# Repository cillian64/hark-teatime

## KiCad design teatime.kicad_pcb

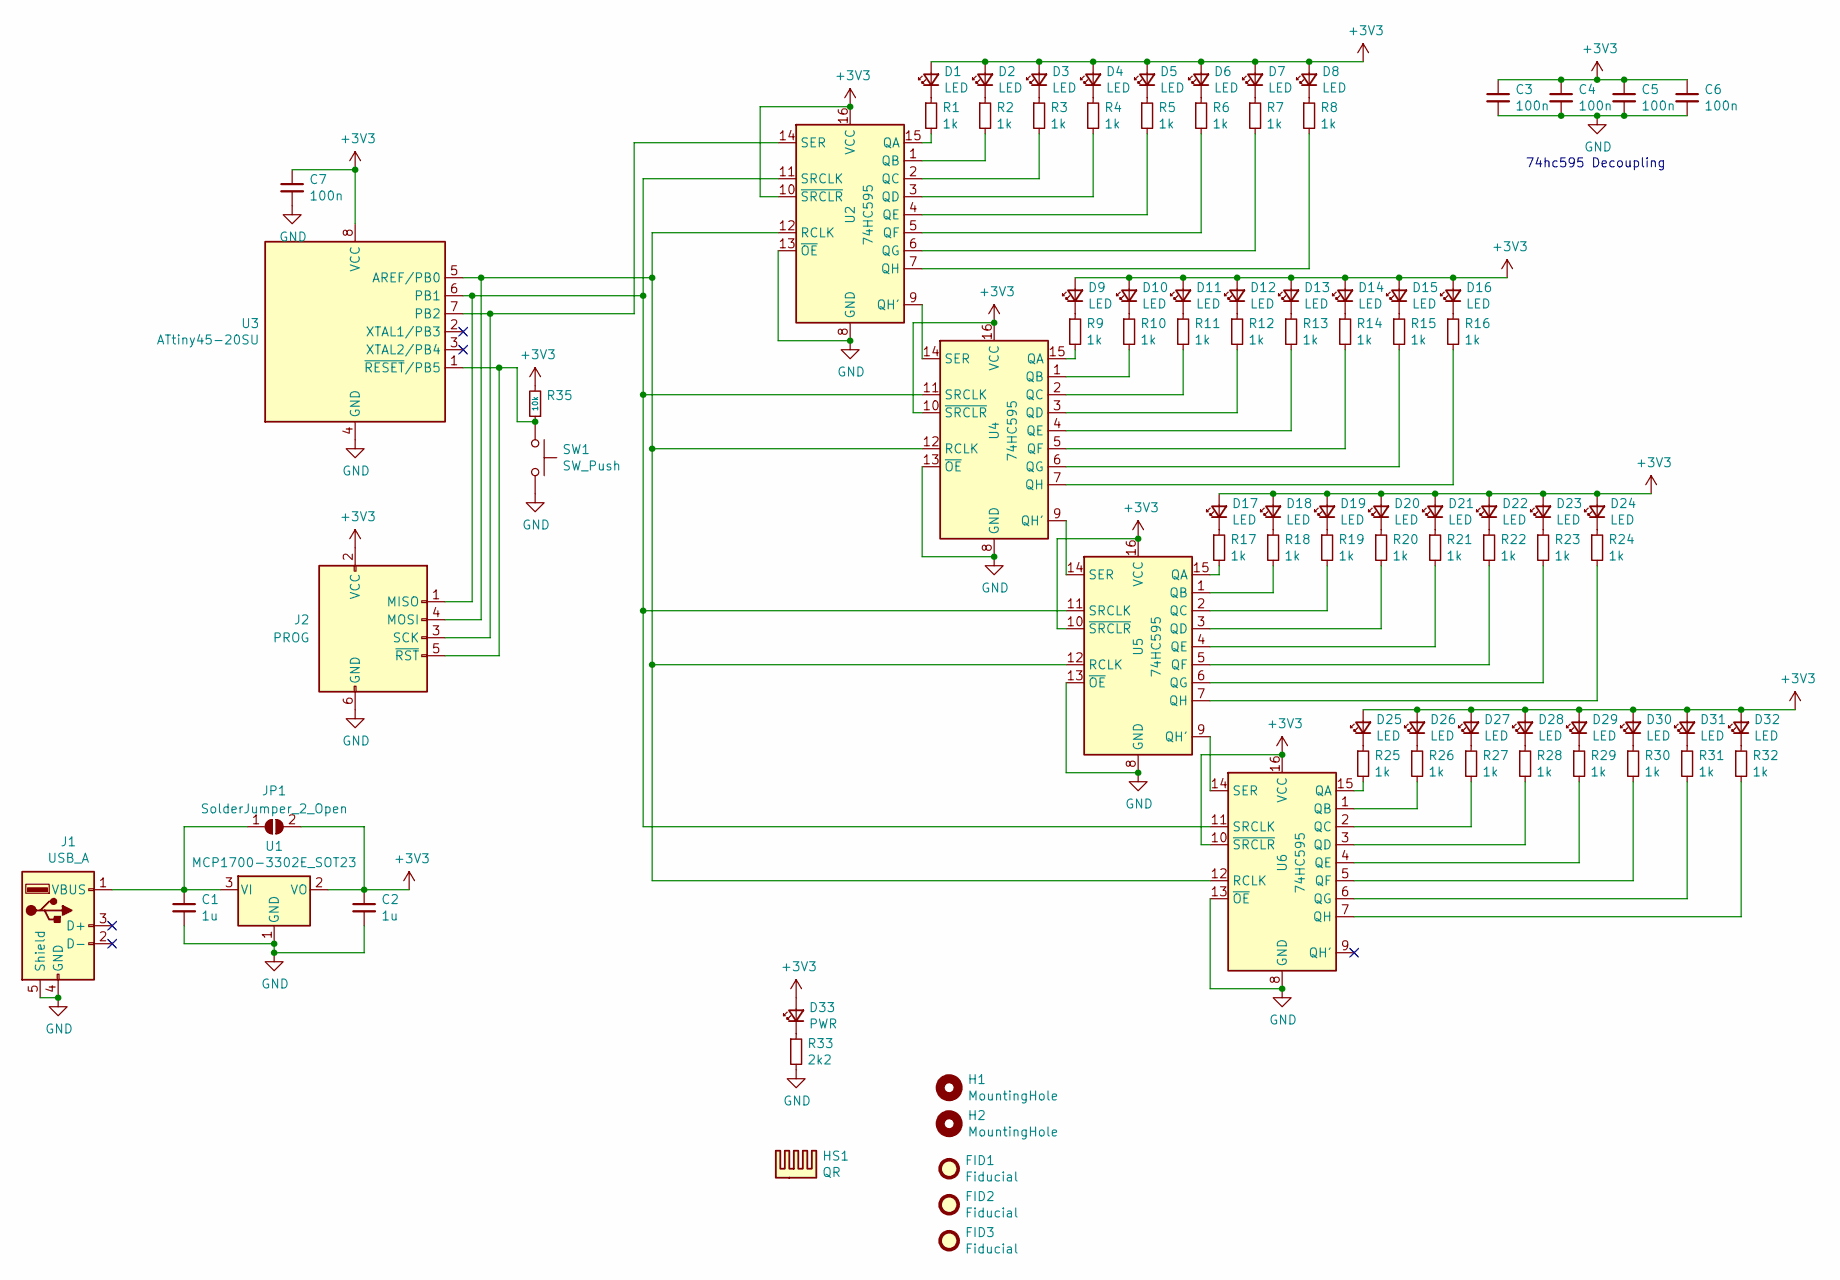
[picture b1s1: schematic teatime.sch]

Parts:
C1, C2: 1u; R_0603_1608Metric; LCSC C105524
C3, C4, C5, C6, C7: 100n; R_0603_1608Metric; Farnell 1141775
D1, D2, D3, D4, D5, D6, D7, D8, D9, D10, D11, D12, D13, D14, D15, D16, D17, D18, D19, D20, D21, D22, D23, D24, D25, D26, D27, D28, D29, D30, D31, D32: LED; LED_0805_2012Metric
D33: PWR; LED_0805_2012Metric
FID1, FID2, FID3: Fiducial; Fiducial_0.75mm_Mask1.5mm
H1, H2: MountingHole; MountingHole_3.2mm_M3
HS1: QR; __github.com_HarkonenBade_teatime
J1: USB_A; USB_A_CNCTech_1001-011-01101_Horizontal_DoubleSided; LCSC C183610
J2: PROG; IDC-Header_2x03_P2.54mm_Vertical
JP1: SolderJumper_2_Open; SolderJumper-2_P1.3mm_Open_RoundedPad1.0x1.5mm
R1, R2, R3, R4, R5, R6, R7, R8, R9, R10, R11, R12, R13, R14, R15, R16, R17, R18, R19, R20, R21, R22, R23, R24, R25, R26, R27, R28, R29, R30, R31, R32: 1k; R_0603_1608Metric
R33: 2k2; R_0603_1608Metric
R35: 10k; R_0603_1608Metric
SW1: SW_Push; SW_PUSH_6mm
U1: MCP1700-3302E_SOT23; SOT-23; LCSC C39051
U2, U4, U5, U6: 74HC595; SOIC-16_3.9x9.9mm_P1.27mm; LCSC C110383
U3: ATtiny45-20SU; SOIJ-8_5.3x5.3mm_P1.27mm; LCSC C62689

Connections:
+3V3: C2.1, C3.1, C4.1, C5.1, C6.1, C7.1, D1.2 (A), D2.2 (A), D3.2 (A), D4.2 (A), D5.2 (A), D6.2 (A), D7.2 (A), D8.2 (A), D9.2 (A), D10.2 (A), D11.2 (A), D12.2 (A), D13.2 (A), D14.2 (A), D15.2 (A), D16.2 (A), D17.2 (A), D18.2 (A), D19.2 (A), D20.2 (A), D21.2 (A), D22.2 (A), D23.2 (A), D24.2 (A), D25.2 (A), D26.2 (A), D27.2 (A), D28.2 (A), D29.2 (A), D30.2 (A), D31.2 (A), D32.2 (A), D33.2 (A), J2.2 (VCC), JP1.2 (B), R35.2, U1.2 (VO), U2.10 (~SRCLR), U2.16 (VCC), U3.8 (VCC), U4.10 (~SRCLR), U4.16 (VCC), U5.10 (~SRCLR), U5.16 (VCC), U6.10 (~SRCLR), U6.16 (VCC)
GND: C1.2, C2.2, C3.2, C4.2, C5.2, C6.2, C7.2, J1.4 (GND), J1.5 (Shield), J2.6 (GND), R33.2, SW1.2, U1.1 (GND), U2.8 (GND), U2.13 (~OE), U3.4 (GND), U4.8 (GND), U4.13 (~OE), U5.8 (GND), U5.13 (~OE), U6.8 (GND), U6.13 (~OE)
unnamed: C1.1, J1.1 (VBUS), JP1.1 (A), U1.3 (VI)
unnamed: D1.1 (K), R1.1
unnamed: D2.1 (K), R2.1
unnamed: D3.1 (K), R3.1
unnamed: D4.1 (K), R4.1
unnamed: D5.1 (K), R5.1
unnamed: D6.1 (K), R6.1
unnamed: D7.1 (K), R7.1
unnamed: D8.1 (K), R8.1
unnamed: D9.1 (K), R9.1
unnamed: D10.1 (K), R10.1
unnamed: D11.1 (K), R11.1
unnamed: D12.1 (K), R12.1
unnamed: D13.1 (K), R13.1
unnamed: D14.1 (K), R14.1
unnamed: D15.1 (K), R15.1
unnamed: D16.1 (K), R16.1
unnamed: D17.1 (K), R17.1
unnamed: D18.1 (K), R18.1
unnamed: D19.1 (K), R19.1
unnamed: D20.1 (K), R20.1
unnamed: D21.1 (K), R21.1
unnamed: D22.1 (K), R22.1
unnamed: D23.1 (K), R23.1
unnamed: D24.1 (K), R24.1
unnamed: D25.1 (K), R25.1
unnamed: D26.1 (K), R26.1
unnamed: D27.1 (K), R27.1
unnamed: D28.1 (K), R28.1
unnamed: D29.1 (K), R29.1
unnamed: D30.1 (K), R30.1
unnamed: D31.1 (K), R31.1
unnamed: D32.1 (K), R32.1
unnamed: D33.1 (K), R33.1
unnamed: J2.1 (MISO), U2.11 (SRCLK), U3.6 (PB1), U4.11 (SRCLK), U5.11 (SRCLK), U6.11 (SRCLK)
unnamed: J2.3 (SCK), U2.14 (SER), U3.7 (PB2)
unnamed: J2.4 (MOSI), U2.12 (RCLK), U3.5 (AREF/PB0), U4.12 (RCLK), U5.12 (RCLK), U6.12 (RCLK)
unnamed: J2.5 (~RST), R35.1, SW1.1, U3.1 (~RESET~/PB5)
unnamed: R1.2, U2.15 (QA)
unnamed: R2.2, U2.1 (QB)
unnamed: R3.2, U2.2 (QC)
unnamed: R4.2, U2.3 (QD)
unnamed: R5.2, U2.4 (QE)
unnamed: R6.2, U2.5 (QF)
unnamed: R7.2, U2.6 (QG)
unnamed: R8.2, U2.7 (QH)
unnamed: R9.2, U4.15 (QA)
unnamed: R10.2, U4.1 (QB)
unnamed: R11.2, U4.2 (QC)
unnamed: R12.2, U4.3 (QD)
unnamed: R13.2, U4.4 (QE)
unnamed: R14.2, U4.5 (QF)
unnamed: R15.2, U4.6 (QG)
unnamed: R16.2, U4.7 (QH)
unnamed: R17.2, U5.15 (QA)
unnamed: R18.2, U5.1 (QB)
unnamed: R19.2, U5.2 (QC)
unnamed: R20.2, U5.3 (QD)
unnamed: R21.2, U5.4 (QE)
unnamed: R22.2, U5.5 (QF)
unnamed: R23.2, U5.6 (QG)
unnamed: R24.2, U5.7 (QH)
unnamed: R25.2, U6.15 (QA)
unnamed: R26.2, U6.1 (QB)
unnamed: R27.2, U6.2 (QC)
unnamed: R28.2, U6.3 (QD)
unnamed: R29.2, U6.4 (QE)
unnamed: R30.2, U6.5 (QF)
unnamed: R31.2, U6.6 (QG)
unnamed: R32.2, U6.7 (QH)
unnamed: U2.9 (QH'), U4.14 (SER)
unnamed: U4.9 (QH'), U5.14 (SER)
unnamed: U5.9 (QH'), U6.14 (SER)

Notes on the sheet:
74hc595 Decoupling

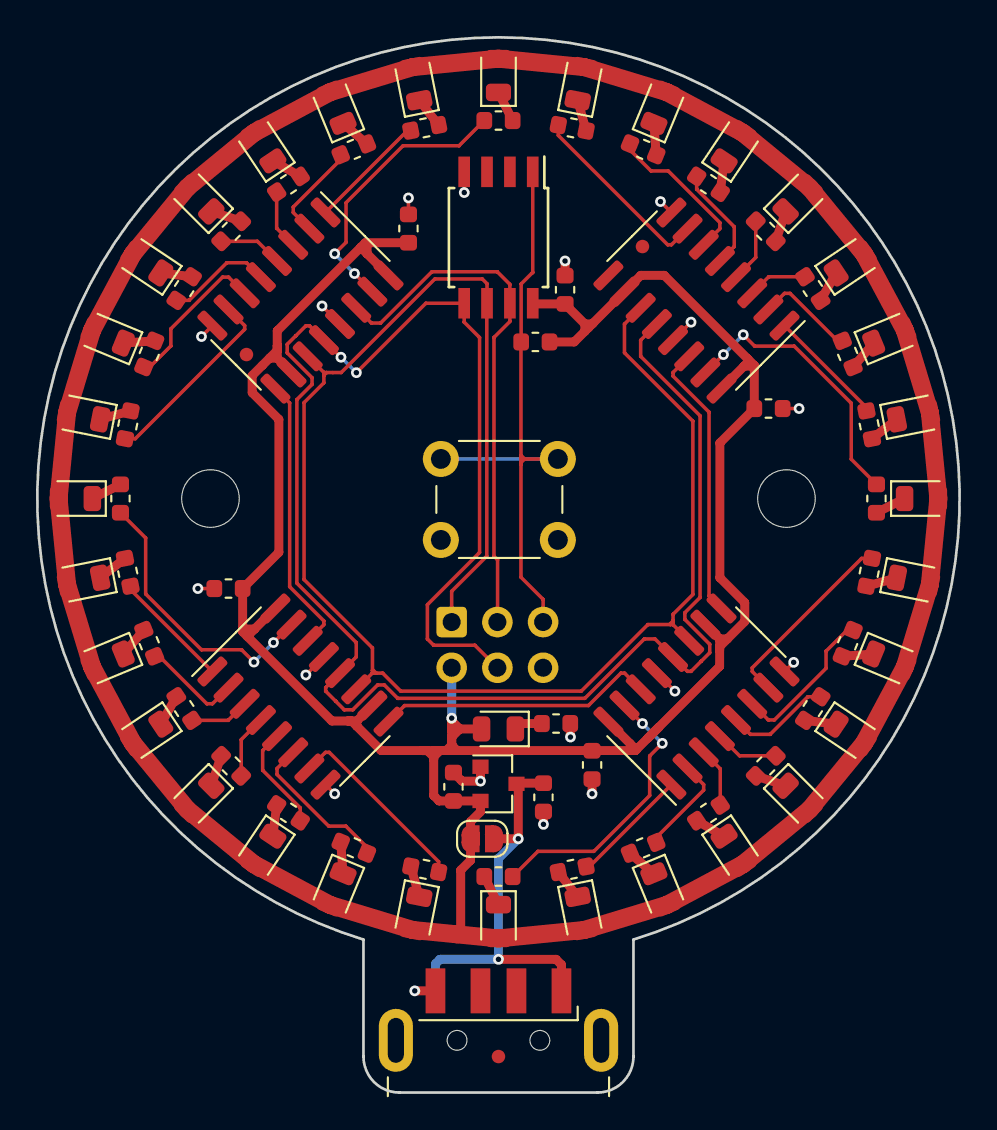
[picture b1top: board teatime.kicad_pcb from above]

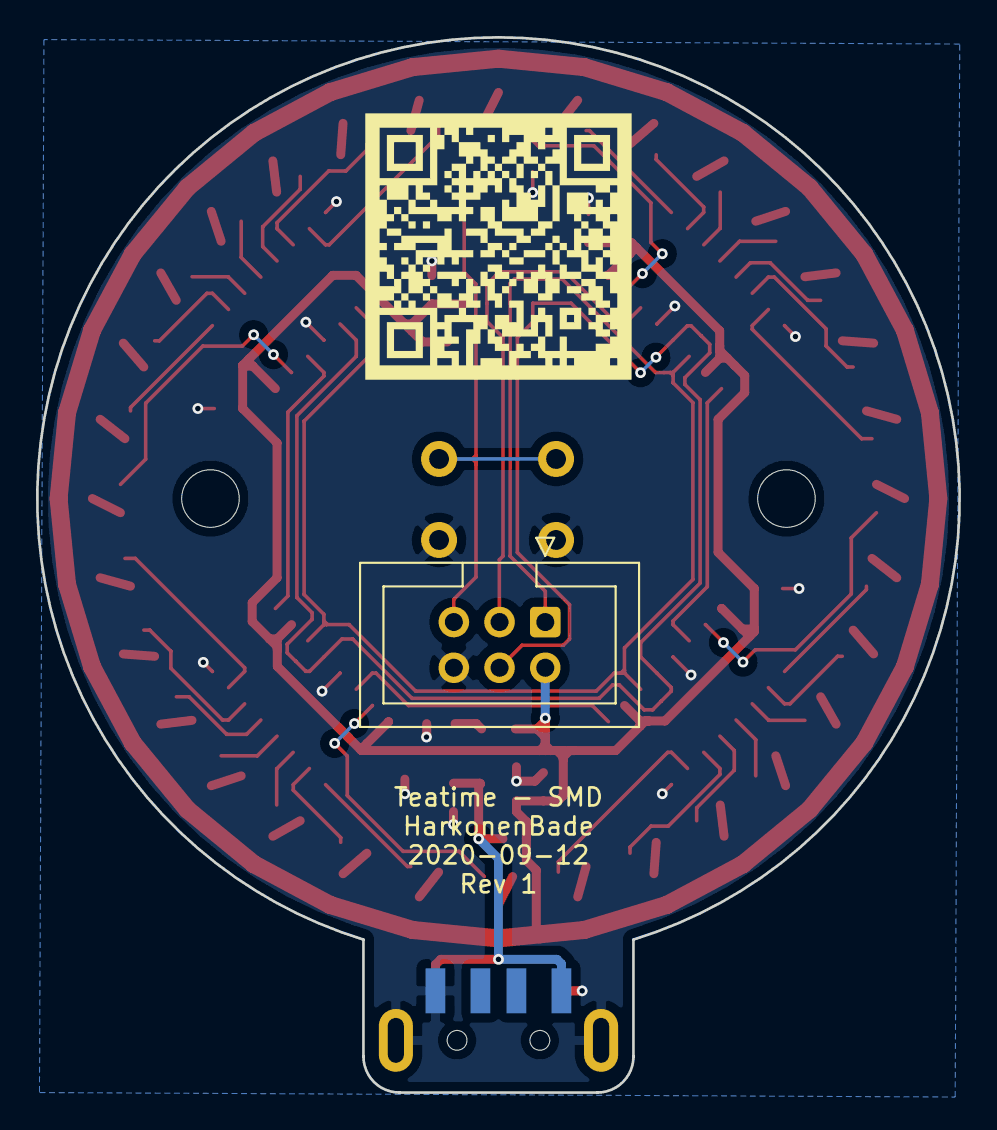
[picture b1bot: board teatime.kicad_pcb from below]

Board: 2 copper layers, 51.2 x 58.6 mm, 90 parts (2 on the bottom side), 75 nets.

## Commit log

2020-02-10 Cur State
2020-02-11 Shift regs and led layout
2020-02-12 Add micro and tweak some other bits
2020-02-12 More tweaks and v1 version of board
2020-02-12 Gerbers, schematic pdf and board svg
2020-02-13 Few slight tweaks to footprints used and updated build files
2020-02-14 Few small tweaks and add silk
2020-02-14 Update gerber zip
2020-02-15 Switch around various bits: * Add decoupling * Omron button * pth caps
2020-02-15 Update generated files
2020-02-15 More updates, added buzzer
2020-03-01 Regen files
2020-09-06 Initial version of firmware
2020-09-07 Improved display loop
2020-10-03 SMD variant board
2020-10-03 Cant decoupling caps over
2020-10-03 Completed board
2020-10-07 Updated display software with new fancier LED trace
2020-10-18 Update Makefile for attiny45 and windows avrdude
    Set MCU to attiny45 for SMD board, update makefile for windows avrdude.exe
    (because good luck getting avrdude to work under WSL with a non-CDC programmer)
